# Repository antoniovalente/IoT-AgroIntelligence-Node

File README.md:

# IoT AgroIntelligence LoRaWAN Node

PCB files of a LoRaWAN node for agriculture use. The node uses a [CubeCell module from Heltec](https://heltec.org/project/htcc-ab01/).
The node has four 12-bit ADC channels, one 18-bit ADC channel, one I2C port, and one SDI-12 port.
It is also possible to connect a 3.6V LiPo battery and the node has an onboard solar energy management system, that can directly connect with a 5.5~7V solar panel.

### Prerequisites

To view the files use Autodesk Eagle (project uses version 9.6.0) 

[Autodesk Eagle](https://www.autodesk.com/products/eagle/free-download) 

## Authors

* **Antonio Valente** - *Initial work* - [Antonio Valente](https://github.com/antoniovalente/)

<!---See also the list of [contributors](https://github.com/your/project/contributors) who participated in this project. --->

## Licenses

The hardware project is licensed under the [CERN Open Hardware Licence](https://ohwr.org/cernohl) - see the [LICENSE.md](LICENSE.md) file for details.

The documentation files are licensed under a [Creative Commons Attribution 4.0 International
License][cc-by] - see the [LICENSE-CC-BY.md](LICENSE.md) file for details

[![CC BY 4.0][cc-by-image]][cc-by]

[cc-by]: http://creativecommons.org/licenses/by/4.0/
[cc-by-image]: https://i.creativecommons.org/l/by/4.0/88x31.png
[cc-by-shield]: https://img.shields.io/badge/License-CC%20BY%204.0-lightgrey.svg

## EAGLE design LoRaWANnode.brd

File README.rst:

IoT AgroIntelligence LoRaWAN Node
=================================

PCB files of a LoRaWAN node for agriculture use. The node uses a
`CubeCell module from Heltec <https://heltec.org/project/htcc-ab01/>`__.
The node has four 12-bit ADC channels, one 18-bit ADC channel, one I2C
port, and one SDI-12 port. It is also possible to connect a 3.6V LiPo
battery and the node has an onboard solar energy management system, that
can directly connect with a 5.5~7V solar panel.

.. figure:: https://github.com/antoniovalente/IoT-AgroIntelligence-Node/blob/master/photos/IoT_AgroIntelligenceNode.jpg
   :alt: IoT Node
   :width: 50%
   :align: center

IoT Node Prerequisites
~~~~~~~~~~~~~~~~~~~~~~~

To view the files use Autodesk Eagle (project uses version 9.6.0)

`Autodesk
Eagle <https://www.autodesk.com/products/eagle/free-download>`__

Authors
-------

-  **Antonio Valente** - *Initial work* - `Antonio
   Valente <https://github.com/antoniovalente/>`__

.. raw:: html

   <!---See also the list of [contributors](https://github.com/your/project/contributors) who participated in this project. --->
   
Articles
--------
MDPI Electronics `"Low-Cost LoRaWAN Node for Agro-Intelligence IoT" <https://www.mdpi.com/741896>`__

Licenses
--------

The hardware project is licensed under the `CERN Open Hardware
Licence <https://ohwr.org/cernohl>`__ - see the
`LICENSE.md <LICENSE.md>`__ file for details.

The documentation files are licensed under a `Creative Commons
Attribution 4.0 International
License <http://creativecommons.org/licenses/by/4.0/>`__ - see the
`LICENSE-CC-BY.md <LICENSE.md>`__ file for details

|CC BY 4.0|

.. |CC BY 4.0| image:: https://i.creativecommons.org/l/by/4.0/88x31.png
   :target: http://creativecommons.org/licenses/by/4.0/

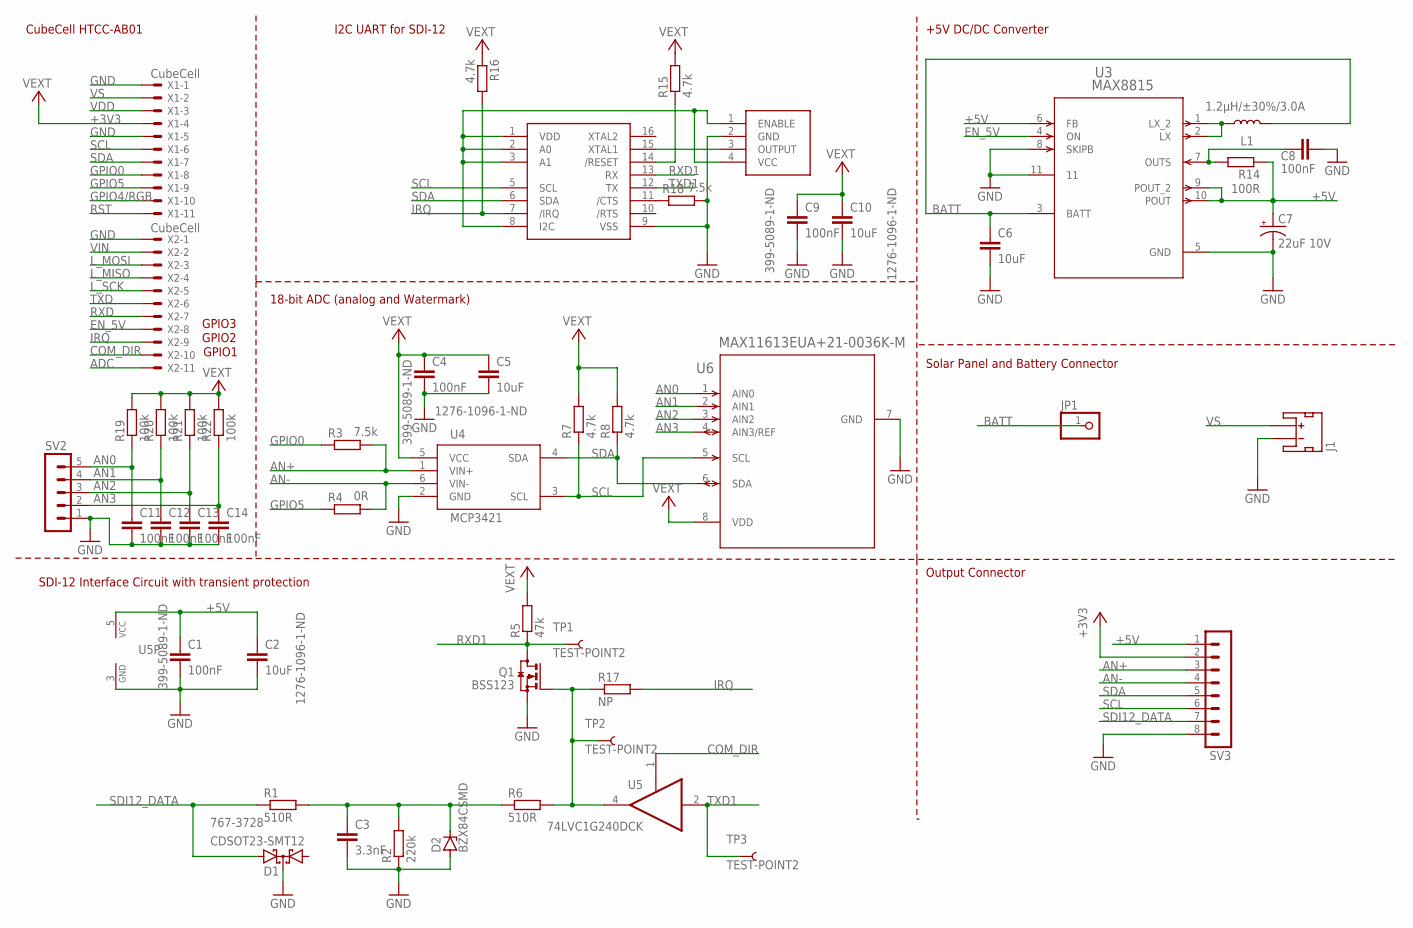
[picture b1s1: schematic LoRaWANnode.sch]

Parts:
C1, C4, C9, C11, C12, C13, C14: 100nF; SCHMALZHAUS_0603-CAP; MPN 06033C104KAT4A
C2, C5, C10: 10uF; SCHMALZHAUS_0603-CAP; MPN 0805ZC106KAT2A
C3: 3.3nF; C0603K
C6: 10uF; 0805
C7: 22uF 10V; EIA3216
C8: 100nF; C0603K
D1: CDSOT23-SMT12; SOT23
D2: BZX84CSMD; TO236
J1: JST_2MM_MALE; JST-2-SMD
JP1: PINHD-1X1CB; 1X01-CLEANBIG
L1: 1.2µH/±30%/3.0A; CR54
Q1: BSS123; SOT23
R1, R6: 510R; R0603
R2: 220k; R0603
R3, R18: 7.5k; R0603
R4: 0R; R0603
R5: 47k; R0603
R7, R8, R15, R16: 4.7k; R0603
R14: 100R; R0603
R17: NP; R0603
R19, R20, R21, R22: 100k; R0603
SV2: MA05-1
SV3: MA08-1
TP1, TP2, TP3: TEST-POINT2; PAD.02X.02
U1: RICKK2_SC16IS740
U2: RICKK2_OSC-KC3225K
U3: MAX8815; 21-0137I_T1033-1-M
U4: MCP3421; SOT23-6; MPN MCP3421A0T-E/CH
U5: 74LVC1G240DCK; SC70-5
U6: MAX11613EUA+21-0036K-M; 21-0036K-M
X1, X2: CubeCell; 22-23-2111

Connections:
+3V3: C4.1, C5.1, C9.1, C10.1, R5.2, R7.2, R8.2, R15.2, R16.1, R19.2, R20.2, R21.2, R22.2, SV3.2, U1.1 (VDD), U1.2 (A0), U1.3 (A1), U1.8 (I2C), U2.1 (ENABLE), U2.4 (VCC), U4.5 (VCC), U6.8 (VDD), X1.4
+5V: C1.1, C2.1, C7.+, R14.1, SV3.1, U3.6 (FB), U3.9 (POUT_2), U3.10 (POUT), U5.5 (VCC)
ADC: X2.11
AN0: C11.1, R19.1, SV2.5, U6.1 (AIN0)
AN1: C12.1, R20.1, SV2.4, U6.2 (AIN1)
AN2: C13.1, R21.1, SV2.3, U6.3 (AIN2)
AN3: C14.1, R22.1, SV2.2, U6.4 (AIN3/REF)
AN+: R3.2, SV3.3, U4.1 (VIN+)
AN-: R4.2, SV3.4, U4.6 (VIN-)
BATT: C6.1, JP1.1, L1.P$2 (2), U3.3 (BATT)
COM_DIR: U5.1 (OE), X2.10
EN_5V: U3.4 (ON), X2.8
GND: C1.2, C2.2, C3.2, C4.2, C5.2, C6.2, C7.-, C8.2, C9.2, C10.2, C11.2, C12.2, C13.2, C14.2, D1.3 (C), D2.A, J1.1 (-), Q1.2 (S), R2.1, R18.2, SV2.1, SV3.8, U1.9 (VSS), U2.2 (GND), U3.5 (GND), U3.8 (SKIPB), U3.11, U4.2 (GND), U5.3 (GND), U6.7 (GND), X1.1, X1.5, X2.1
GPIO0: R3.1, X1.8
GPIO4/RGB: X1.10
GPIO5: R4.1, X1.9
IRQ: R16.2, R17.2, U1.7 (/IRQ), X2.9
L_MISO: X2.4
L_MOSI: X2.3
L_SCK: X2.5
unnamed: C3.1, D2.C, R1.2, R2.2, R6.1
unnamed: C8.1, R14.2, U3.7 (OUTS)
unnamed: U1.15 (XTAL1), U2.3 (OUTPUT)
unnamed: L1.P$1 (1), U3.1 (LX_2), U3.2 (LX)
unnamed: R18.1, U1.11 (/CTS)
unnamed: R15.1, U1.14 (/RESET)
unnamed: Q1.1 (G), R6.2, R17.1, TP2.P$1, U5.4 (O)
RST: X1.11
RXD: X2.7
RXD1: Q1.3 (D), R5.1, TP1.P$1, U1.13 (RX)
SCL: R7.1, SV3.6, U1.5 (SCL), U4.3 (SCL), U6.5 (SCL), X1.6
SDA: R8.1, SV3.5, U1.6 (SDA), U4.4 (SDA), U6.6 (SDA), X1.7
SDI12_DATA: D1.2 (A2), R1.1, SV3.7
TXD: X2.6
TXD1: TP3.P$1, U1.12 (TX), U5.2 (I)
VDD: X1.3
VIN: X2.2
VS: J1.2 (+), X1.2

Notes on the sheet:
CubeCell HTCC-AB01
I2C UART for SDI-12
+5V DC/DC Converter
18-bit ADC (analog and Watermark)
Solar Panel and Battery Connector
Output Connector
SDI-12 Interface Circuit with transient protection
GPIO1
GPIO2
GPIO3

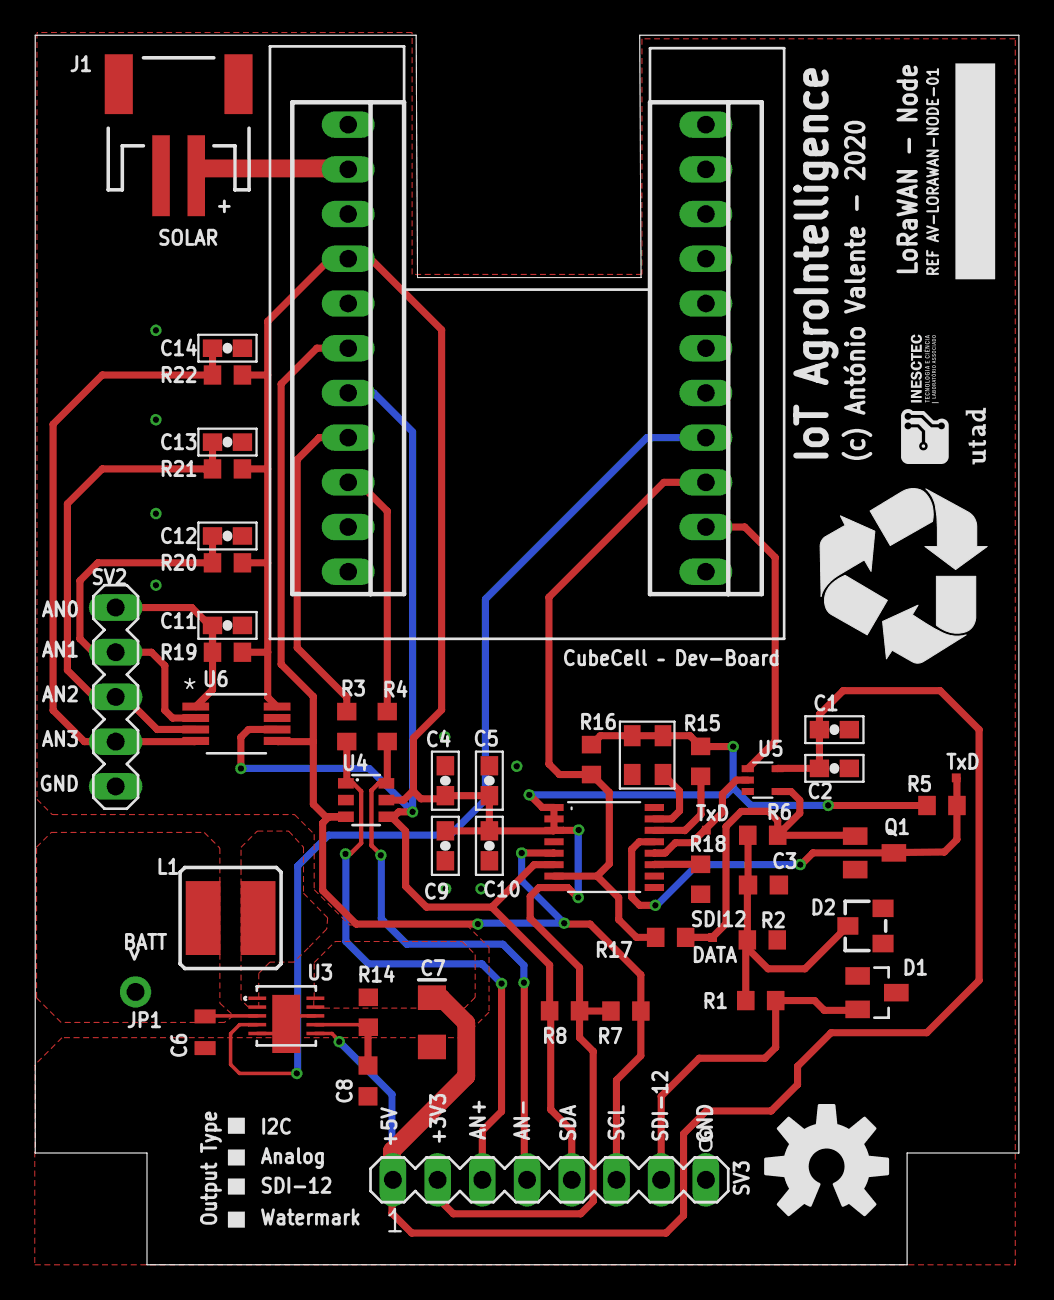
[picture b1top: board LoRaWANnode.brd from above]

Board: 2 copper layers, 55.9 x 69.8 mm, 54 parts (0 on the bottom side), 28 nets.

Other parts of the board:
U$1: INESCTEC_5MM
U$2: UTAD_NEW_5MM
U$3: RECYCLING_10.00
U$4: OSHW-LOGO-L

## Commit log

2020-05-22 Create LICENSE
2020-05-22 Rename LICENSE to LICENSE.md
2020-05-27 Rename README.rst to README.md

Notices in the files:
parts and their libraries:
SparkFun-Connectors: Licensing: Creative Commons ShareAlike 4.0 International - https://creativecommons.org/licenses/by-sa/4.0
